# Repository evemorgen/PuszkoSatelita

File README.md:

# To jest repo w którym trzymamy wszystkie pliki zwiącane z projektem CanSat #

## Struktura organizacyjna: ##
1. dokumentacja
    - folder *dokumentacja* służy do trzymania dokumentacji projektu, kolejnych jej iteracji, oraz ostatecznych wersji na PDR, CDE, FDR
2. code
    - folder *code* służy do trzymania jakiegokolwiek kodu, czy to arduino czy coś co będzie obrabiać dane potem itd.
3. elektronika
    - folder *elektronika* służy do trzymania schematów eagle dla projektu, ewentualnie innych dziwnych rzeczy związanych z elektroniką.

## Media społecznościowe ##
  * [Facebook](https://www.facebook.com/JJCanSatTeam/)

  * [WordPress](https://jjcansat.wordpress.com)

And remember, before asking

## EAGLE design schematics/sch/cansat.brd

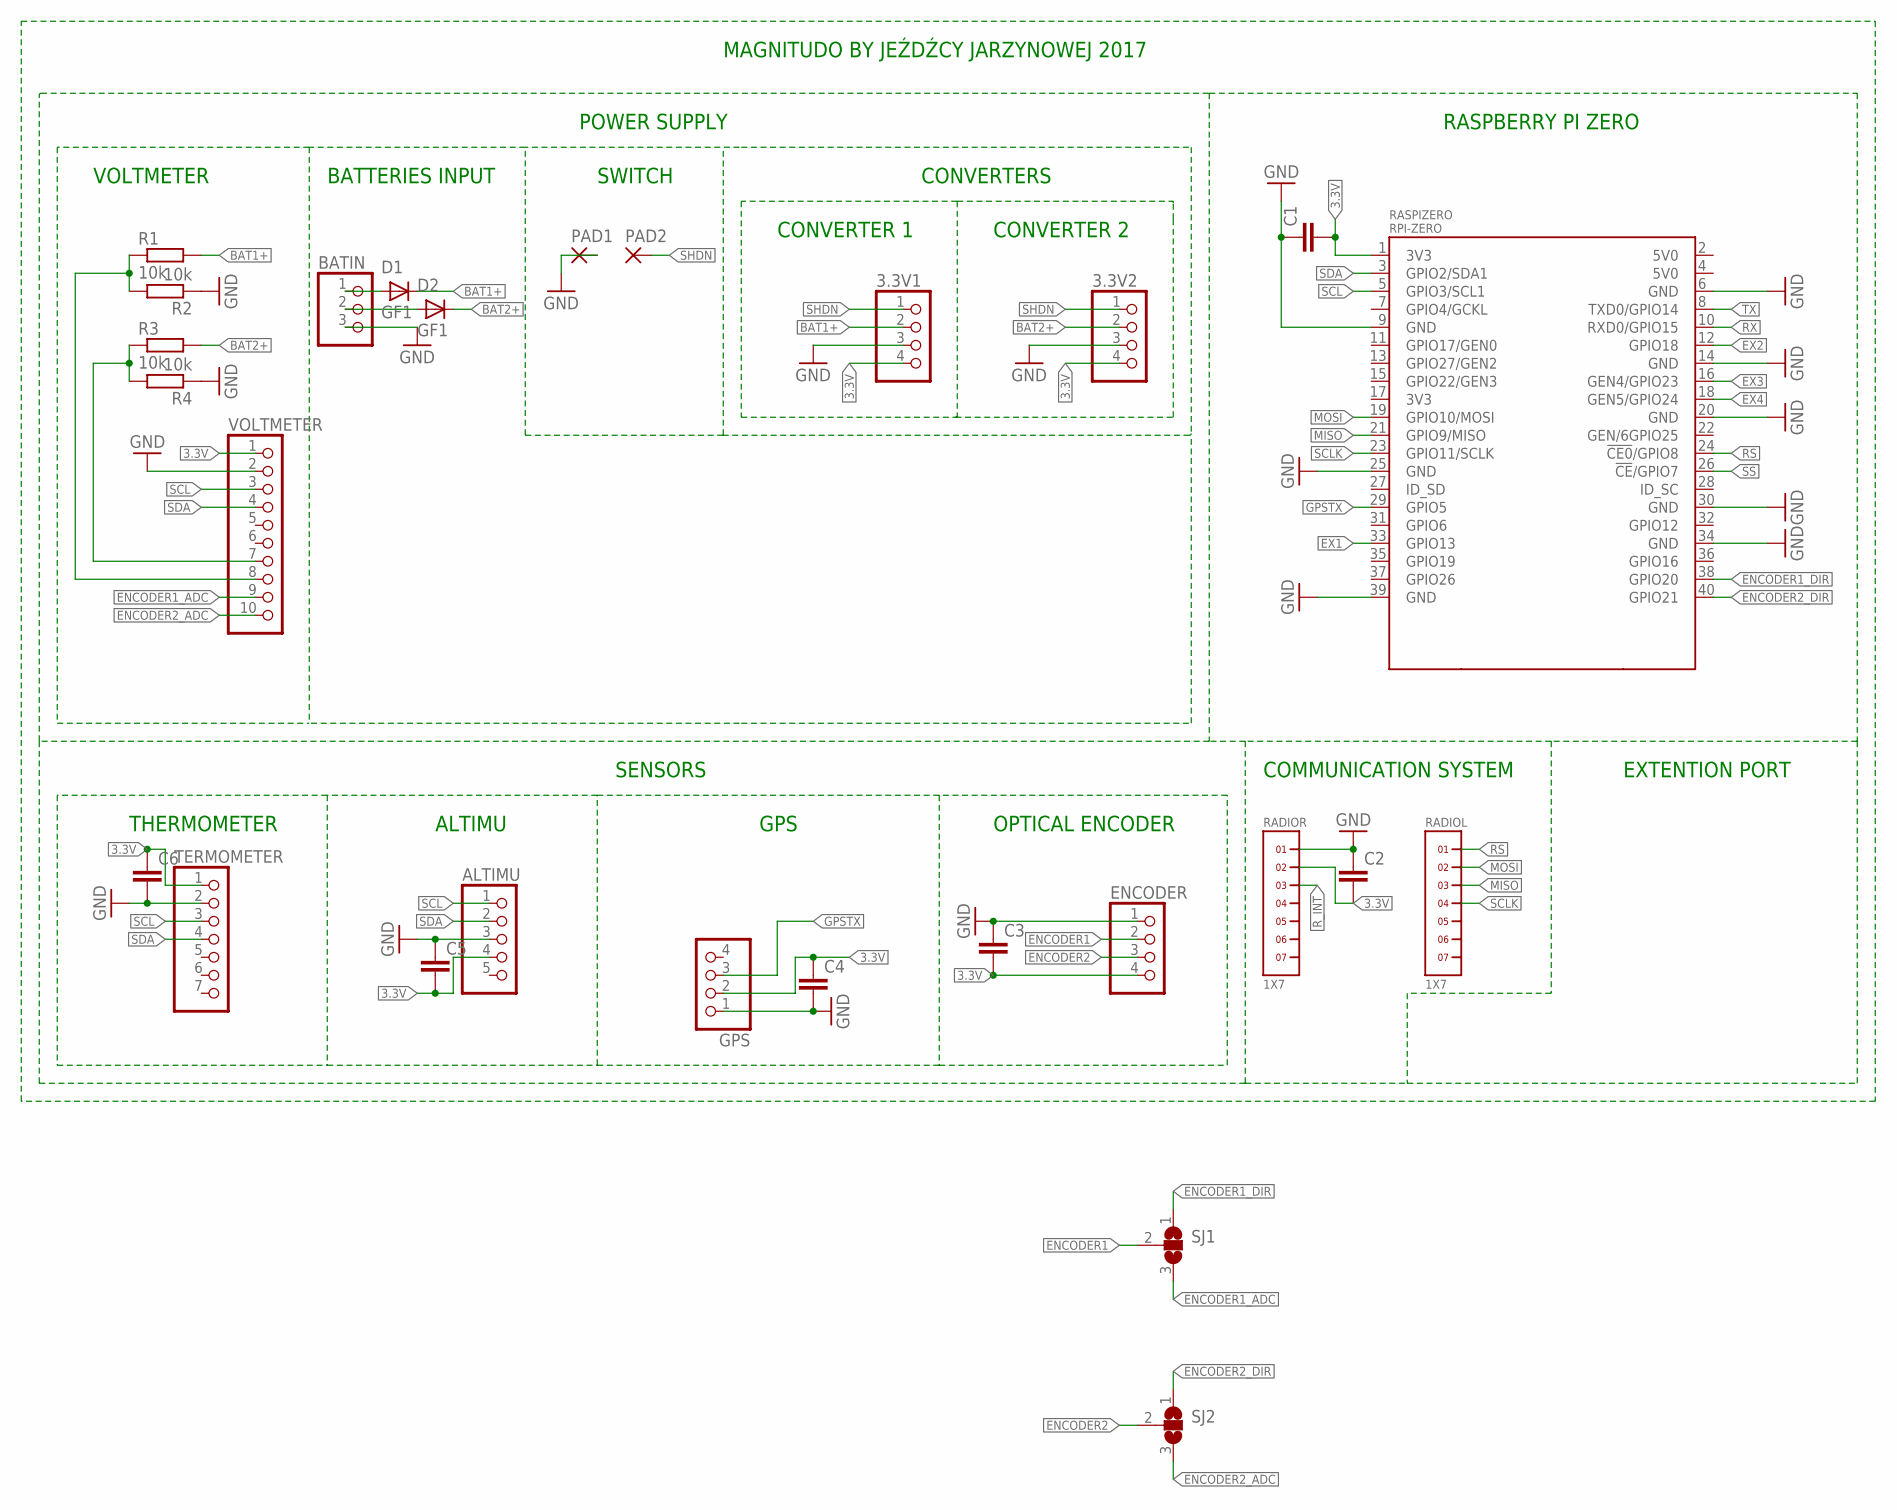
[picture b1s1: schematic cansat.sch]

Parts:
3.3V1, 3.3V2: PINHD-1X4; 1X04
ALTIMU: PINHD-1X5; 1X05
BATIN: PINHD-1X3; 1X03
C1, C2, C3, C4, C5, C6: CC1206; C1206
D1, D2: GF1; SMA-DO214AC
ENCODER: PINHD-1X4; 1X04
GPS: PINHD-1X4; 1X04
PAD1, PAD2: WIREPADSMD5-2,5; 5-2,5
R1, R2, R3, R4: 10k; R1206
RADIOL: 1X7
RADIOR: 1X7
RASPIZERO: RPI-ZERO; RASPBERRYPI_BASTELSTUBE_V13_RASPI_BOARD_B+_FULL
SJ1, SJ2: SJ2WW; SJ_2W
TERMOMETER: PINHD-1X7; 1X07
VOLTMETER: PINHD-1X10; 1X10

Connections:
3.3V: 3.3V1.4, 3.3V2.4, ALTIMU.4, C1.2, C2.2, C3.2, C4.1, C5.2, C6.1, ENCODER.4, GPS.2, RADIOR.2, RASPIZERO.1 (3V3), TERMOMETER.1, VOLTMETER.1
BAT1+: 3.3V1.2, D1.K (C), R1.2
BAT2+: 3.3V2.2, D2.K (C), R3.2
ENCODER1: ENCODER.2, SJ1.2
ENCODER1_ADC: SJ1.3, VOLTMETER.9
ENCODER1_DIR: RASPIZERO.38 (GPIO20), SJ1.1
ENCODER2: ENCODER.3, SJ2.2
ENCODER2_ADC: SJ2.3, VOLTMETER.10
ENCODER2_DIR: RASPIZERO.40 (GPIO21), SJ2.1
EX1: RASPIZERO.33 (GPIO13)
EX2: RASPIZERO.12 (GPIO18)
EX3: RASPIZERO.16 (GEN4/GPIO23)
EX4: RASPIZERO.18 (GEN5/GPIO24)
GND: 3.3V1.3, 3.3V2.3, ALTIMU.3, BATIN.3, C1.1, C2.1, C3.1, C4.2, C5.1, C6.2, ENCODER.1, GPS.1, PAD1.1, R2.1, R4.1, RADIOR.1, RASPIZERO.6 (GND), RASPIZERO.9 (GND), RASPIZERO.14 (GND), RASPIZERO.20 (GND), RASPIZERO.25 (GND), RASPIZERO.30 (GND), RASPIZERO.34 (GND), RASPIZERO.39 (GND), TERMOMETER.2, VOLTMETER.2
GPSTX: GPS.3, RASPIZERO.29 (GPIO5)
MISO: RADIOL.3, RASPIZERO.21 (GPIO9/MISO)
MOSI: RADIOL.2, RASPIZERO.19 (GPIO10/MOSI)
unnamed: R1.1, R2.2, VOLTMETER.8
unnamed: R3.1, R4.2, VOLTMETER.7
unnamed: BATIN.1, D1.A
unnamed: BATIN.2, D2.A
RS: RADIOL.1, RASPIZERO.24 (!CE0!/GPIO8)
RX: RASPIZERO.10 (RXD0/GPIO15)
R_INT: RADIOR.3
SCL: ALTIMU.1, RASPIZERO.5 (GPIO3/SCL1), TERMOMETER.3, VOLTMETER.3
SCLK: RADIOL.4, RASPIZERO.23 (GPIO11/SCLK)
SDA: ALTIMU.2, RASPIZERO.3 (GPIO2/SDA1), TERMOMETER.4, VOLTMETER.4
SHDN: 3.3V1.1, 3.3V2.1, PAD2.1
SS: RASPIZERO.26 (!CE!/GPIO7)
TX: RASPIZERO.8 (TXD0/GPIO14)

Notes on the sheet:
BATTERIES INPUT
SWITCH
POWER SUPPLY
RASPBERRY PI ZERO
CONVERTERS
CONVERTER 1
CONVERTER 2
SENSORS
COMMUNICATION SYSTEM
THERMOMETER
ALTIMU
GPS
OPTICAL ENCODER
MAGNITUDO BY JEŹDŹCY JARZYNOWEJ 2017
EXTENTION PORT
VOLTMETER

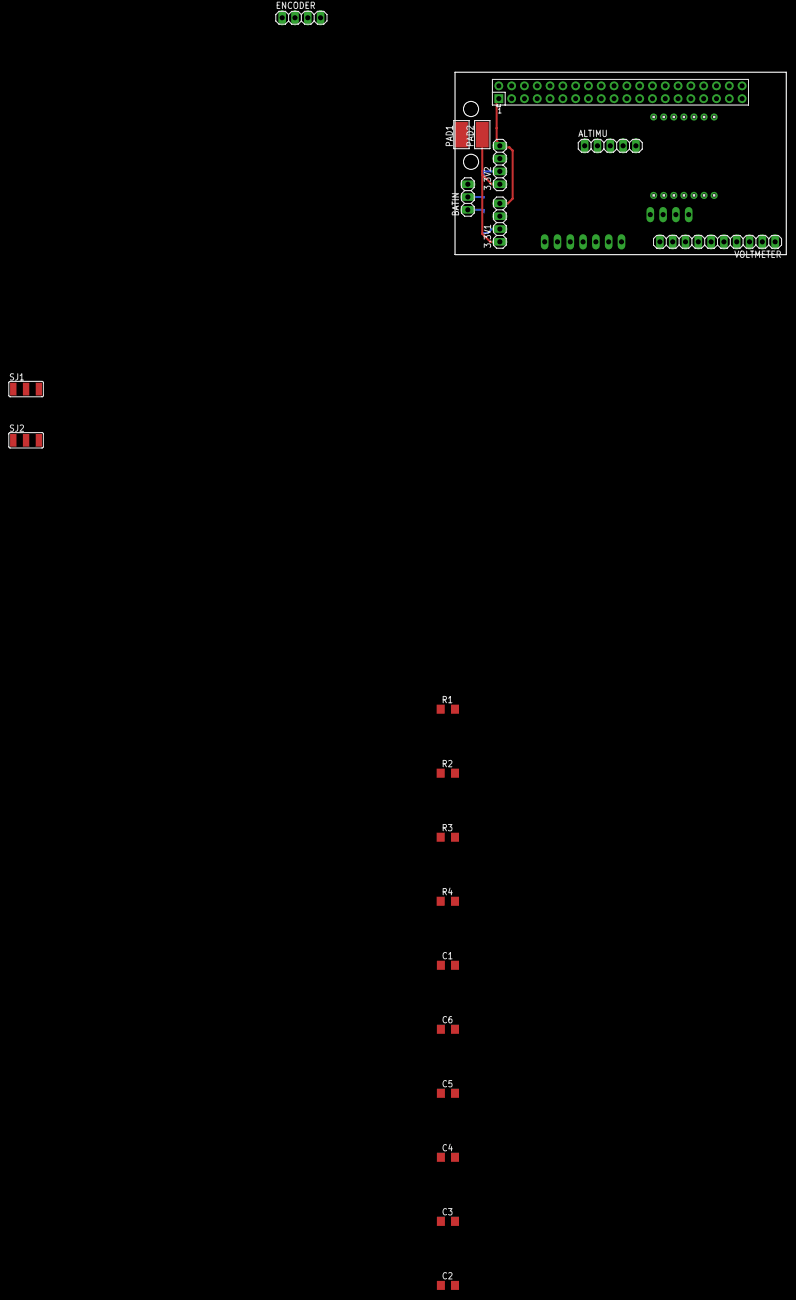
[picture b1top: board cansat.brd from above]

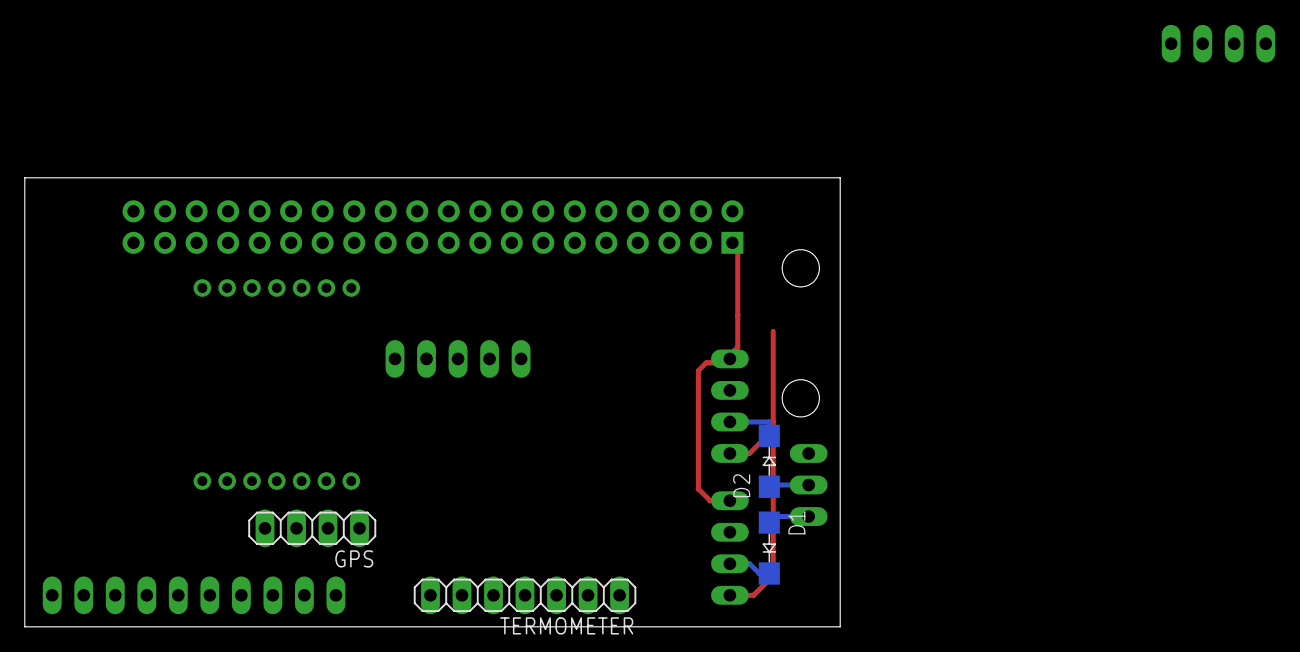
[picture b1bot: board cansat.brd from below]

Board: 2 copper layers, 65.7 x 36.2 mm, 27 parts (4 on the bottom side), 22 nets.

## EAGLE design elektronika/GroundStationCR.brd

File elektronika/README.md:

# Tutaj trzymamy wszelkiego rodzaju pliki związane z elektroniką #
W późniejszym czasie należy uzupełniać readme o dodatkowe sekcje, np opis podstruktury

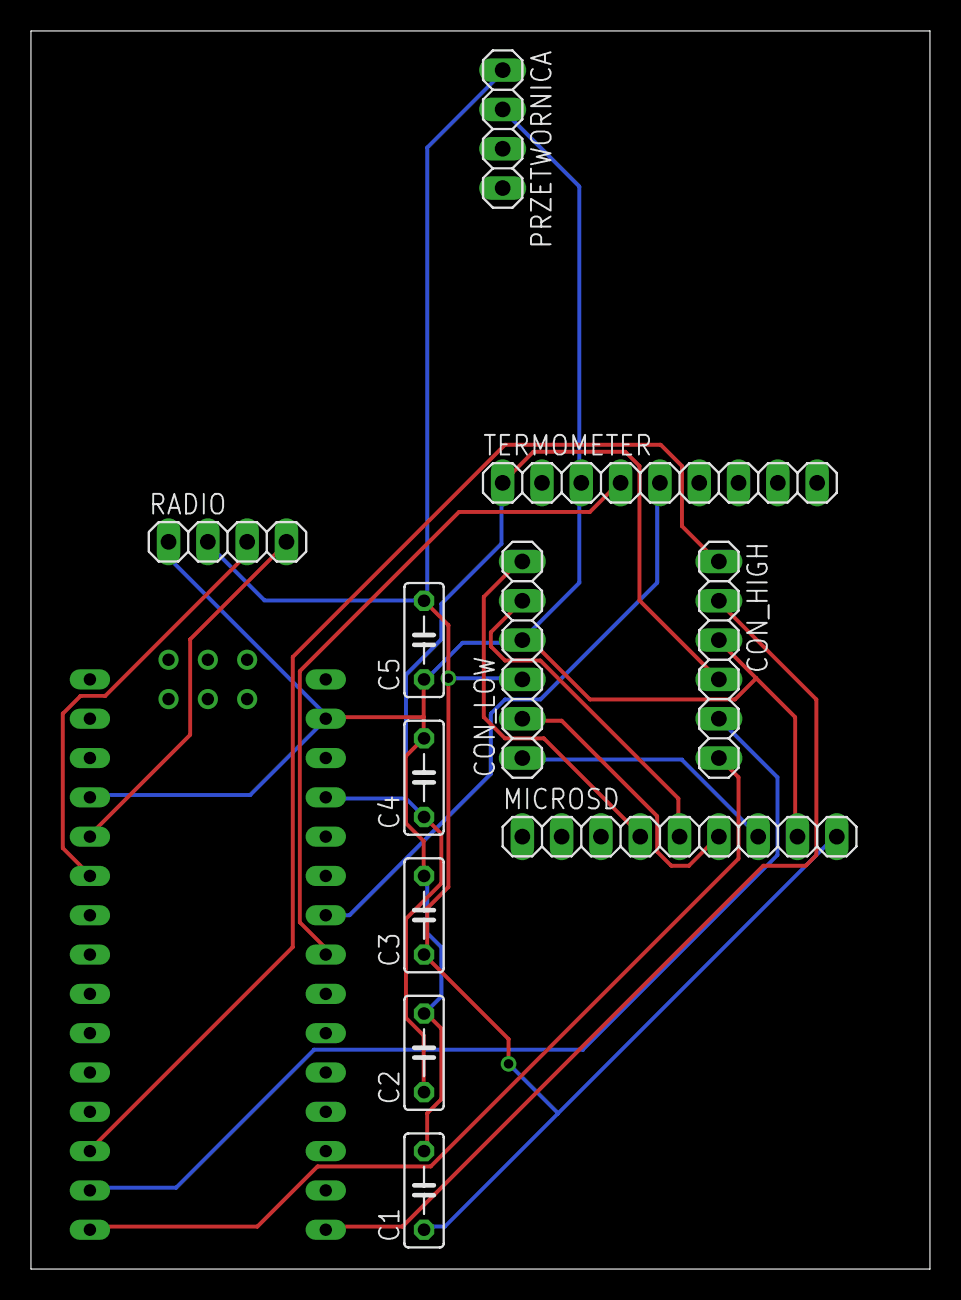
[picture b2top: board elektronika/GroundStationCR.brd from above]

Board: 2 copper layers, 58.1 x 80.0 mm, 12 parts (0 on the bottom side), 15 nets.

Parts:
C1, C2, C3, C4, C5: C050-025X075
CON_HIGH: 1X06
CON_LOW: 1X06
MICROSD: 1X09
PRZETWORNICA: 1X04
RADIO: 1X04
TERMOMETER: 1X09
U$1: NANO

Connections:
3.3V: C1.1, C3.1, C5.2, CON_LOW.3, MICROSD.9, PRZETWORNICA.1, RADIO.2
+5V: C2.1, C4.1, CON_HIGH.4, TERMOMETER.1, U$1.5V
CS: CON_HIGH.1, U$1.D10
CS_L: CON_LOW.6, MICROSD.4
GND: C1.2, C2.2, C3.2, C4.2, C5.1, CON_HIGH.3, CON_LOW.4, MICROSD.8, PRZETWORNICA.2, RADIO.1, TERMOMETER.3, U$1.GND, U$1.GND1
MISO: CON_HIGH.6, U$1.D12
MISO_L: CON_LOW.1, MICROSD.7
MOSI: CON_HIGH.5, U$1.D11
MOSI_L: CON_LOW.2, MICROSD.6
RX: RADIO.3, U$1.D3
SCL: TERMOMETER.5, U$1.A5
SCLK: CON_HIGH.2, U$1.D13
SCLK_L: CON_LOW.5, MICROSD.5
SDA: TERMOMETER.4, U$1.A4
TX: RADIO.4, U$1.D2

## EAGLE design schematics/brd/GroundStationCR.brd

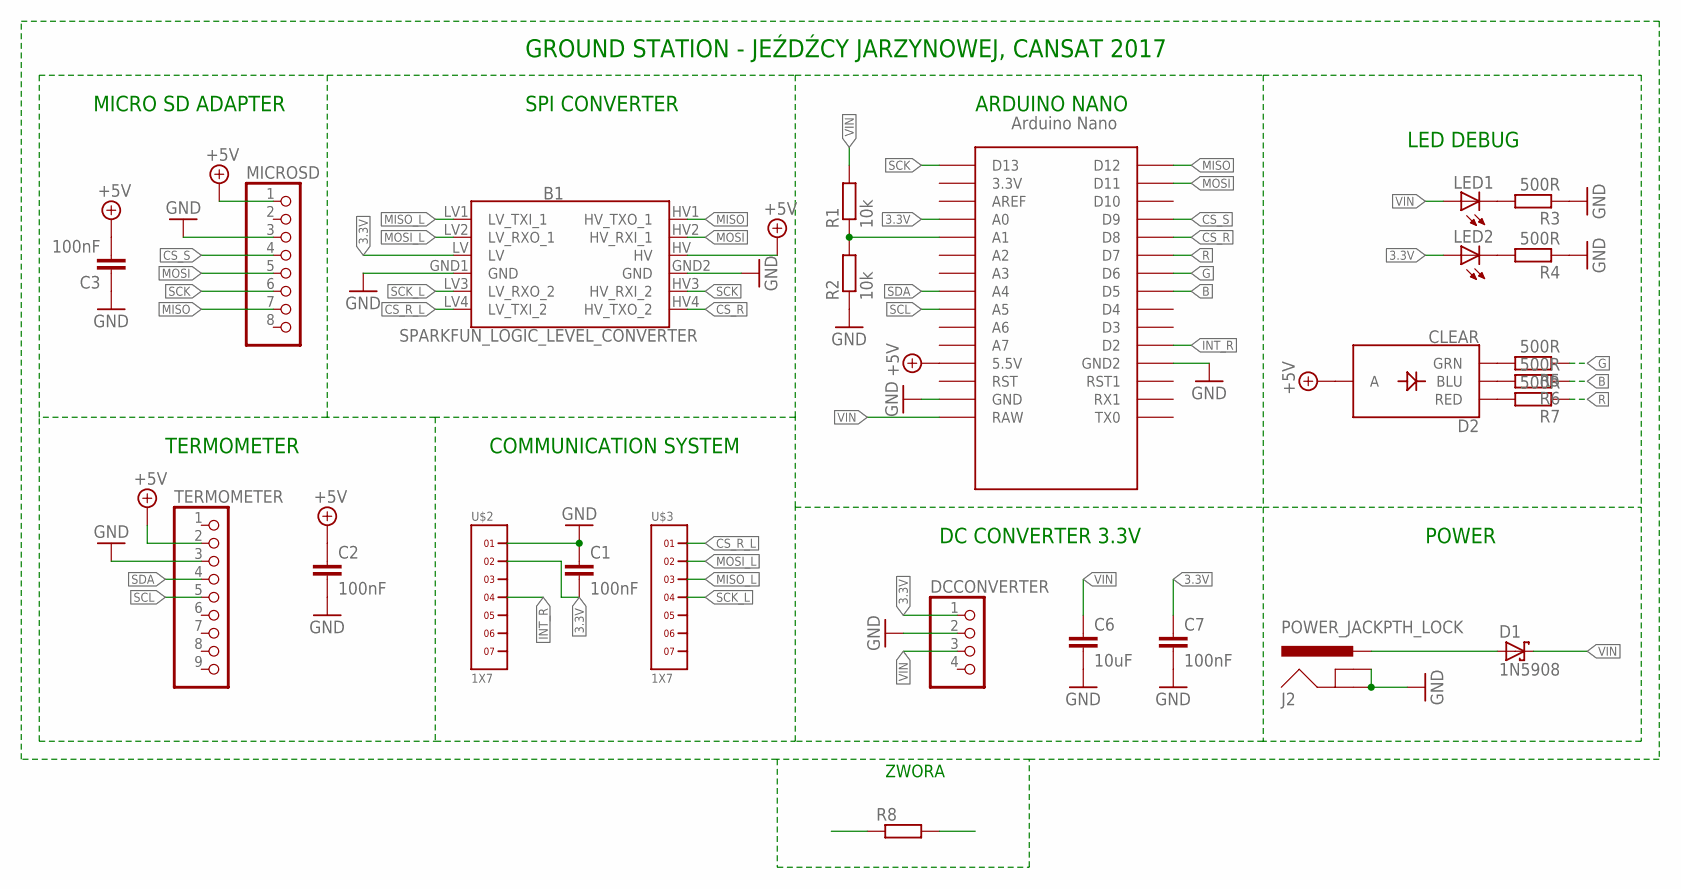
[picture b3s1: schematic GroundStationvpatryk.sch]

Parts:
B1: SPARKFUN_LOGIC_LEVEL_CONVERTER
C1, C2, C3, C7: 100nF; C050-025X075
C6: 10uF; C050-025X075
D1: 1N5908; C4111-15
D2: CLEAR; LED-RGB-THRU
DCCONVERTER: PINHD-1X4; 1X04
J2: POWER_JACKPTH_LOCK; POWER_JACK_PTH_LOCK
LED1, LED2: LED3MM
MICROSD: PINHD-1X8; 1X08
R1, R2: 10k; 0207/7
R3, R4, R5, R6, R7: 500R; 0207/7
R8: R-EU_0207/5V; 0207/5V
TERMOMETER: PINHD-1X9; 1X09
U$1: NANO
U$2, U$3: 1X7

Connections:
3.3V: B1.LV, C1.2, C7.1, DCCONVERTER.1, LED2.A, U$1.A0, U$2.2
+5V: B1.HV, C2.1, C3.2, D2.2 (A), MICROSD.1, TERMOMETER.2, U$1.5V (5.5V)
B: R6.1, U$1.D5
CS_R: B1.HV4 (HV_TXO_2), U$1.D8
CS_R_L: B1.LV4 (LV_TXI_2), U$3.1
CS_S: MICROSD.4, U$1.D9
G: R5.1, U$1.D6
GND: B1.GND1 (GND), B1.GND2 (GND), C1.1, C2.2, C3.1, C6.2, C7.2, DCCONVERTER.2, J2.GND, J2.GNDBREAK, MICROSD.3, R2.1, R3.1, R4.1, TERMOMETER.3, U$1.GND, U$1.GND1 (GND2), U$2.1
INT_R: U$1.D2, U$2.4
MISO: B1.HV1 (HV_TXO_1), MICROSD.7, R8.1, R8.2, U$1.D12
MISO_L: B1.LV1 (LV_TXI_1), U$3.3
MOSI: B1.HV2 (HV_RXI_1), MICROSD.5, U$1.D11
MOSI_L: B1.LV2 (LV_RXO_1), U$3.2
unnamed: D1.A, J2.PWR
unnamed: R1.1, R2.2, U$1.A1
unnamed: LED1.K (C), R3.2
unnamed: LED2.K (C), R4.2
unnamed: D2.3 (GRN), R5.2
unnamed: D2.4 (BLU), R6.2
unnamed: D2.1 (RED), R7.2
R: R7.1, U$1.D7
SCK: B1.HV3 (HV_RXI_2), MICROSD.6, U$1.D13
SCK_L: B1.LV3 (LV_RXO_2), U$3.4
SCL: TERMOMETER.5, U$1.A5
SDA: TERMOMETER.4, U$1.A4
VIN: C6.1, D1.C, DCCONVERTER.3, LED1.A, R1.2, U$1.RAW

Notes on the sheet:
ARDUINO NANO
MICRO SD ADAPTER
TERMOMETER
COMMUNICATION SYSTEM
DC CONVERTER 3.3V
GROUND STATION - JEŹDŹCY JARZYNOWEJ, CANSAT 2017
SPI CONVERTER
POWER
LED DEBUG
ZWORA

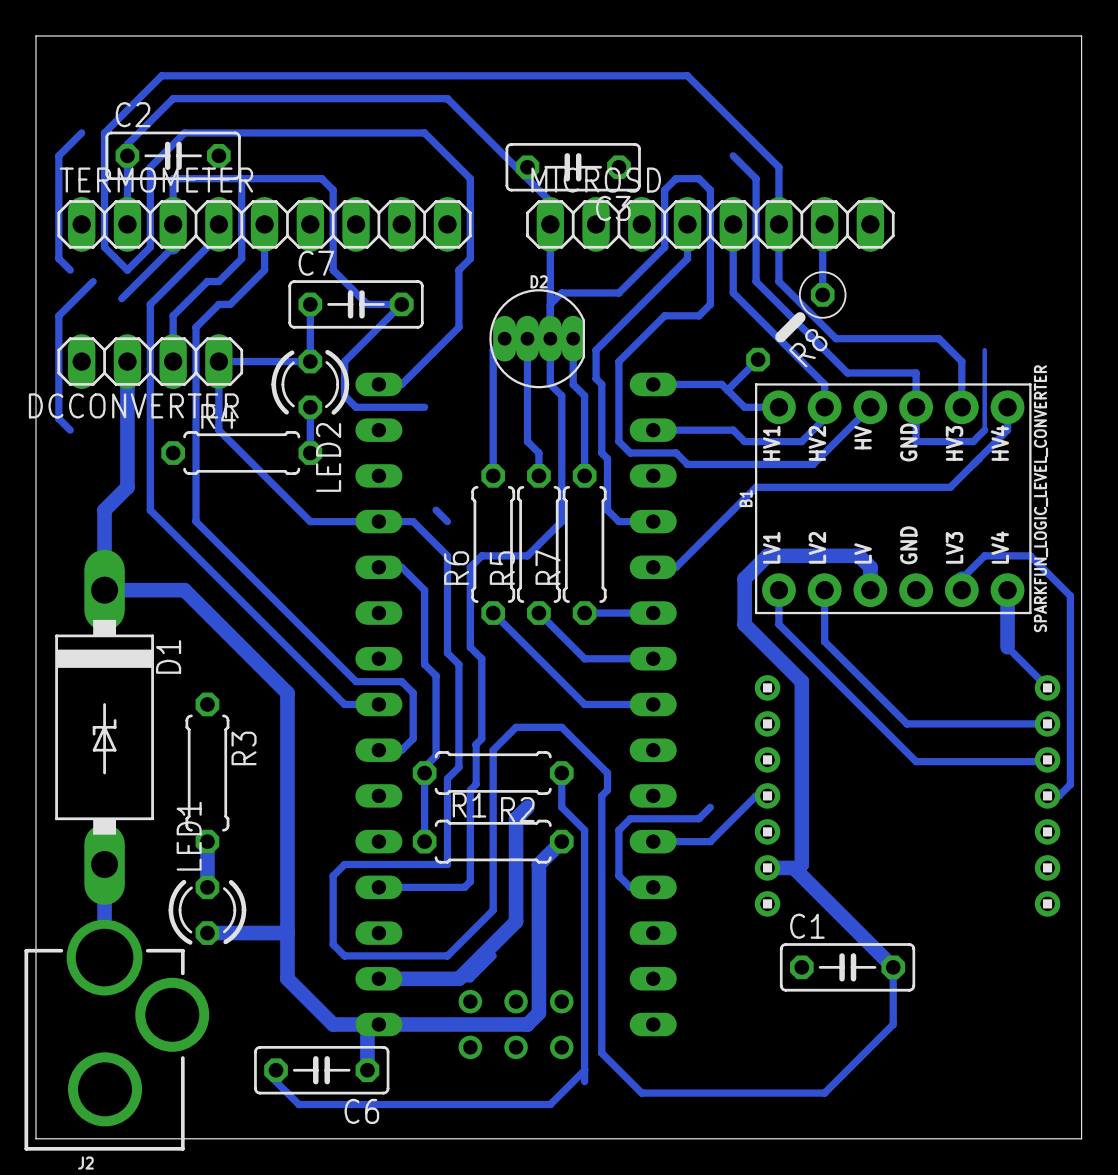
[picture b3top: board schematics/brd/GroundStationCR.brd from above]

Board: 2 copper layers, 58.1 x 61.3 mm, 25 parts (0 on the bottom side), 26 nets.

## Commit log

2016-09-24 first commit, dir structure + readme files
2016-09-24 meme at front page
2016-09-24 small fix
2016-09-24 centering image
2016-09-24 centering image x2
2016-09-24 fix broken link
2016-09-26 dodałem testy integracyhne
2016-10-04 files from esero presentation
2016-10-04 readme update
2016-10-08 Dodanie celów misji do dokumentacji
2016-10-08 Poprawienie zepsutego markdowna
2016-10-08 Dodanie pliku z elementami konstrukcyjnymi, modyfikacja README i wrzucenie plikow do podfolderu
2016-10-08 Dodany plik z linkami to portali spolecznosciowych
2016-10-08 Dodanie mediow spoleczenosciowych do glownego readme
2016-10-08 Poprawione cele misji
2016-10-08 Poprawione linki
2016-10-08 Jednak teraz
2016-10-08 Ostateczne rozwiaznie sprawy linkowej
2016-10-13 Specyfikacja spadochrony
2016-10-13 Fix czytelność
2016-10-15 Podział obowiązków
    Zamieszczam podział obowiązków w zespole.
2016-10-15 Podział obowiązków
    Fixed missing Paweł Biłko
2016-10-15 Update organizacja.md
    Fixed electronics and mechanics tasks assignment
2016-10-18 Specyfikacja spadochronu
2016-10-19 index fix in parachute document
2016-10-19 doc -> pdf
2016-10-21 czesci z docsow
2016-10-24 to_delphi
    Propozycja współpracy dla Delphi Poland S.A.
2016-10-29 Update organizacja.md
    Replaced Stanio with Jan
2016-10-31 2.5.
2016-11-06 Start the cansat code
2016-11-06 Corrige = to == on 14 line
2016-11-14 Create the base of the project
2016-11-16 Mission control
    Set up projektu
2016-11-30 Misc dir pushed
2016-12-07 working(almost) thermometer-module prototype
2016-12-07 Formatting
2016-12-07 Random number generator and read index
2016-12-09 Pierwsza wersja aplikacji
2016-12-29 Kod Stacji Bazowej
    Kod Stacji Bazowej, testy dla radia
2017-01-02 some code changes i guess
2017-01-03 New files
    Commi
2017-01-03 Base station
    Zestaw minimalny.
    https://sourceforge.net/projects/sdpo-cl/ (zewnętrzny komponent niezbędny do zainstalowania w IDE)
2017-01-04 remove swear words
2017-01-08 GroundStation
2017-01-08 errors correction + prettify
2017-01-09 First draft of changed thermometer class
2017-01-09 Modify logging (from file to commandline output)
2017-01-09 Further modification of logging
2017-01-09 Switched back to the initial testing (delay is int to try, except)
2017-01-09 Corrected the use of a non existent variable
2017-01-12 JSON protocol
2017-01-15 Little experiment
2017-01-15 Initial commit with first dependency
2017-01-15 Changed dependency for using GPIO
2017-01-15 Quick check with example
2017-01-15 Corrections
2017-01-15 Bug correction i guess
2017-01-16 Checking if it really works by switching pins
2017-01-17 Raport bez podpisu
2017-01-18 Change of temp sensor
2017-01-18 Test case
2017-01-18 Mismatched types
2017-01-18 Poprawa
2017-01-19 Switched lib third time
2017-01-24 Base Station Application
    JSON implemantation included
2017-02-17 Accelerometer code copied from the github with modifications
2017-02-17 Change the test file code
2017-02-17 Code changes
2017-02-17 removed empty files, added simple temperature/humidity read implementation from Adafruit driver. declared temperature_read() returning temperature in deg C and humidity_read() in %
2017-02-19 Changes to be committed: new file: altimu/altimu.py new file: altimu/altimu.pyc new file: altimu/functions.py new file: altimu/functions.pyc new file: thermometer_humidity_sensor/Adafruit_SHT31.pyc n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
2017-02-19 Added humidity reading based on code for thermometer. Changes required: implement python daemon, because calling python script from bash every iteration is slow.
2017-02-19 Implemented main loop and data flushout directly in python Current speed accessible is about 10Hz
    Changes to be committed:
    modified: Adafruit_SHT31.pyc
    modified: SHT31.pyc
    modified: SHT31_humidity_reader.py
    new file: SHT31_humidity_reader.sh
    modified: SHT31_temperature_reader.py
2017-02-19 Removed trash Changes to be committed: deleted: Adafruit_SHT31.pyc deleted: SHT31.pyc deleted: SHT31d_start.sh
2017-02-19 First tests of IMU using nice library found on github. test2.py works, gotta figure out data meaning.
2017-02-20 Bash script to grab the only interesting (newest line) from GPS On branch GPS Changes to be committed: new file: grab_gps_line.sh
2017-02-20 removed cat from line grabber to prevent pipe breaking
2017-02-21 Receiver code, absolutely basic, throws message from LoRa@433.8MHz and RSSI to serial Changes to be committed: new file: LoRa.h new file: LoRaReceiver.ino
2017-02-21 Found working LoRa library. Tested and performed well with 5 short transmits per second. Base for future development.
2017-02-23 Radio testing scripts, usable to harvest some code from.
2017-02-23 Implemented GPS logger (lat,long,height,accuracy,time) like the one in thermometer Changes to be committed: new file: gps.py new file: gps.pyc new file: gps_reader.py new file: grab_datetime_line.sh
2017-02-23 Changes not staged for commit: modified: test.py deleted: test2.py
2017-02-23 migrating
2017-02-23 trash removal
2017-02-23 Fixed test.py
2017-02-23 test now became main read function holder added reader to store data Thermometer/gps-style in ~/data
2017-02-26 fixes
2017-02-26 schematics files
    schematics of the ground station & cansat
2017-02-26 minor fixes
2017-02-26 minor changes
    minor changes
2017-02-26 Receiver code
    Includes received data parser (to JSON), not tested
2017-02-27 Added radio_transmitter.py - base for further development. Found out that minimum transmission time is 0.3s for 127B payload
2017-02-27 Minor Coding Rate changes
2017-02-27 cansat main board
2017-02-28 Implemented payload generator with single byte checksum
2017-02-28 Quick fix of checksum
2017-02-28 Implemented 2B checksum and file reader.
2017-02-28 Changed CR, made it work. Found out buggy TXes were hardware issue, 100uF capacitor @ radio power supply fixed them well.
2017-02-28 removed debug TX
2017-02-28 removed debug lines
2017-02-28 removed LED support causing warnings to sys stdout
2017-02-28 cansat board fixed
2017-03-01 optocoupler on radio/gps vcc
2017-03-01 Opis tworzenia obrazu w md
2017-03-01 Corrected errors and added polish version.
2017-03-01 Formatting errors
2017-03-02 aggregator slowly growing
2017-03-02 bug fixes
2017-03-02 fixed bug causing file to stay open for too long
2017-03-02 fixed bug showing existance of nonexisting file
2017-03-02 features
2017-03-02 aggregator now sends floats as raw bytes instead of human-readable string
2017-03-03 compressed date to daywise format, year and month ommited
2017-03-05 few changes
    deleted algorithm of parsing receied data, saving sensor data once a 10
    seconds, errors send by standard frame
2017-03-05 Version with raw bytes and checksum computing
2017-03-05 Dziedzic's checksum algorithm
    Dziedzic's checksum algorithm
2017-03-06 made file executable
2017-03-06 created starting script
2017-03-06 bug fixes and non-relative file paths implementation
2017-03-06 rm'ed old sh scripts, surpressed data flow
2017-03-07 improved overall stability with file closing
2017-03-07 stability thru delay between data collection and transmission
2017-03-11 GPIO mods
2017-03-22 New battery voltage reading function
2017-03-22 Readers for 2 batts
2017-03-22 added voltage support
2017-03-23 wind-speed sensor driver
2017-03-23 Made working daemon
2017-03-23 added new sensors based on ADC
2017-03-27 Ground Station
    Ground Station code
2017-03-29 LS331 (?)
    hipotetical code that SHOULD work
2017-03-29 added service required for gps fix
2017-03-29 added software serial support
2017-03-31 remove none libs files
2017-03-31 remove more files
2017-03-31 remove pyc files
2017-03-31 altimu.py back to master version
2017-03-31 cleanup
2017-03-31 remove gps files
2017-03-31 fixin gps stuff
2017-03-31 remove not libs files
2017-04-04 purger
2017-04-04 wind support
2017-04-04 Meh, connected it directly to dedicated UART
2017-04-04 disbaled GPS software serial support
2017-04-04 removed GPS softw. serial
2017-04-05 added radio stamp reset
2017-04-05 camera service
2017-04-05 camera support
2017-04-06 fixes applied
2017-04-06 resolution fix
2017-04-06 Fixed missing file after merge/changed freq to 433.6
2017-04-07 recalib
2017-04-07 more fixes
2017-04-07 +x, add missing file
2017-04-07 Per second reads applied
2017-04-07 install script
2017-04-07 changed timestamp resolution
2017-04-07 logging
2017-04-07 stuff

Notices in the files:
parts and their libraries:
sparkfun-led: Licensing: Creative Commons ShareAlike 4.0 International - https://creativecommons.org/licenses/by-sa/4.0
